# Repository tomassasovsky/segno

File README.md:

<p align="center">
  <picture>
    <source media="(prefers-color-scheme: dark)" srcset="tool/brand_assets/segno-glyph-white.svg">
    
  </picture>
</p>

<h1 align="center">Segno</h1>

<p align="center">
  A live looping instrument: a foot-operated console, two touch screens, and a
  native audio engine on a Raspberry Pi 5.
</p>

<p align="center">

</p>

Segno records a phrase, plays it back in a loop, and lets you layer more parts
over it while you keep playing. It is built as a dedicated appliance rather than
a desktop app: the musician works it with ten footswitches and an encoder,
reads it from a 15.6-inch main screen and a 7-inch readout, and never needs a
computer on stage.

This repository holds the Flutter application, the C audio engine, the console
firmware and the Yocto image that boots the appliance. The circuit boards and
the sheet-metal enclosure are in
[segno-hardware](https://github.com/tomassasovsky/segno-hardware), and the
design file in [segno-design](https://github.com/tomassasovsky/segno-design).

## What it does

- **Loops on eight tracks** in two banks of four, with record, overdub, undo
  and redo per track, mute, solo, pan, fades and reverse.
- **Five loop modes.** Multi, Sync, Song, Band and Free decide how track
  lengths relate and whether sections play together or one at a time. Tempo,
  time signature, click and count-in apply to all of them.
- **Effects** written in portable C, arranged as single effects or racks, and
  placed on live inputs, on recorded tracks, or on the outputs.
- **Virtual instruments** played from MIDI, recorded like any other input.
- **Backing tracks** that play alongside the loops.
- **A library** of saved sessions and audio, on internal storage or a USB
  drive, with search, folders, preview and backup.
- **Performance recording** to multitrack stems, with export to an Ableton
  Live set and a Mac companion app, [Segno Transfer](apps/segno_transfer/README.md),
  to download recordings over the network.
- **Control from anywhere on stage:** the built-in footswitches, external
  footswitches and expression pedals on two jacks, and MIDI over USB and DIN.
- **An appliance that maintains itself:** A/B system updates that roll back on
  failure, Wi-Fi setup, storage management and a tuner.

| Library | Loop modes |
|---|---|
|  |  |

The screenshots are renders from the application's own screenshot tests.

## Hardware

The console is a welded aluminum wedge. Its faceplate carries ten
footswitches with LED indicators (Record/Play, Stop, Undo, Mode, Track 1 to 4,
Clear and Bank), an encoder inside a 35-pixel LED ring, and the two screens.
Inside are a Raspberry Pi 5 with NVMe storage, a USB audio interface, and the
console board: a custom PCB with an RP2350 (Raspberry Pi Pico 2) that reads
the switches and drives the lights over a UART link to the Pi. The board also
provides DIN MIDI in and out, two jacks for external pedals, and USB-C Power
Delivery input.

The console firmware is a thin client. It reports raw switch, encoder and pedal
events and renders the LED frames the application sends back; all looper
behavior lives in the application.

See [segno-hardware](https://github.com/tomassasovsky/segno-hardware) for the board designs, enclosure generator
and manufacturing package, and [firmware/](firmware/README.md) for the
microcontroller code.

## Architecture

```mermaid
flowchart LR
  subgraph console["Console board (RP2350)"]
    fw["Firmware: switches, encoder, LEDs, pedal jacks"]
  end
  subgraph pi["Raspberry Pi 5, Yocto image"]
    ui["Flutter UI and blocs<br/>lib/"]
    repo["Repositories<br/>packages/*_repository"]
    engine["Audio engine in C<br/>packages/segno_engine"]
  end
  audio["USB audio interface"]
  fw <-- "UART link" --> repo
  ui --> repo --> engine
  engine <-- "miniaudio" --> audio
```

- **Application** (`lib/`). Flutter, using the bloc pattern. It runs under the
  ivi-homescreen embedder directly on DRM/KMS, one engine per screen.
- **Repositories and clients** (`packages/`). The domain layer between the UI
  and the hardware: looper state, sessions, settings, pedals, MIDI, storage,
  updates, Wi-Fi. Presentation never talks to a data client directly.
- **Audio engine** (`packages/segno_engine`). A hand-written C engine on
  [miniaudio](https://miniaud.io). The audio callback never allocates or
  blocks; the UI sends commands through a lock-free ring and reads state from
  snapshots. Dart reaches it through FFI.
- **Appliance image** (`deploy/yocto`). A Yocto build for the Raspberry Pi 5
  with RAUC A/B updates. CI builds and publishes each image.

## Repository layout

| Path | Contents |
|---|---|
| [`lib/`](lib) | The Flutter application |
| [`packages/`](packages) | Repositories, data clients and the audio engine, each with its own README |
| [`apps/segno_transfer/`](apps/segno_transfer/README.md) | Mac app for downloading performance recordings |
| [`firmware/`](firmware/README.md) | Console board and LED ring firmware |
| [`deploy/`](deploy/README.md) | Yocto layer and appliance image configuration |
| [`docs/`](docs/README.md) | Status, design records and file-format specifications |
| [`test/`](test) | Application tests, including the screenshot tests |

Two sibling repositories hold the rest of the project:
[segno-hardware](https://github.com/tomassasovsky/segno-hardware) has the PCBs
(KiCad), the enclosure generator (Python/CadQuery) and the manufacturing files,
and [segno-design](https://github.com/tomassasovsky/segno-design) has the
design's history and studies. The UI design itself is a Penpot file on a
self-hosted Penpot server; segno-design keeps snapshots of it, and the
earlier Pencil file (`segno-ui.pen`), now frozen.

## Building

Segno targets the appliance. A Mac can run the application for development,
and the mock flavor runs it without any audio hardware.

Requirements: Flutter 3.50, Xcode for the macOS host, and a C compiler for
the engine tests.

```sh
flutter pub get
flutter run -d macos --flavor development -t lib/main_mock.dart
```

Tests:

```sh
flutter test                                              # application
bash packages/segno_engine/src/test/run_native_tests.sh   # audio engine (C)
bash firmware/test/run_tests.sh                           # console link contract
```

Each package under `packages/` has its own tests; see its README. Building the
appliance image is described in [deploy/yocto](deploy/yocto/README.md), and
installing it on a Raspberry Pi in [docs/RUNNING_ON_RPI.md](docs/RUNNING_ON_RPI.md).

## Status

Segno is under active development by one person and has not had a stable
release. The application and engine run on the appliance, and experimental
images are published as
[pre-releases](https://github.com/tomassasovsky/segno/releases). The console
enclosure is designed and awaiting fabrication. Work is tracked in
[GitHub Issues](https://github.com/tomassasovsky/segno/issues), and
[docs/PROGRESS.md](docs/PROGRESS.md) records what has been built.

## Contributing

Bug reports and pull requests are welcome. Read
[CONTRIBUTING.md](CONTRIBUTING.md) first, and see [SECURITY.md](SECURITY.md)
for reporting vulnerabilities.

## License

Segno is free software, licensed under the
[GNU General Public License v3.0 or later](LICENSE). Third-party code under
`packages/segno_engine/third_party/` keeps its own licenses.

Created by [Tomás Sasovsky](https://github.com/tomassasovsky).

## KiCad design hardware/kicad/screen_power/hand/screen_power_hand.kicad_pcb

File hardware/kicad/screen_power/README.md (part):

<!-- cspell:words unreviewed -->
<!-- cspell:words IRLZ NPBF Schurter upsize -->
<!-- cspell:words fanout -->
<!-- cspell:words preorder Axicom Mbps energization Digi typec mrico kilohm -->
<!-- cspell:words overvoltage derate autosuspend overmolds fanouts onsemi Nexperia Omron derating autoroutes pulldowns -->
<!-- cspell:words SUP SUM Rds backfeed Micro pulldown Vgs Littelfuse Lumberg MMBT DMODEL stackup microstrip heatsinks eleUniverse ATOF PXCN FHAC overcurrent -->
# Screen power and touch switch

**Revision P** removes two obsolete ground-fill exclusions beside mounting
hole H1, restoring its smooth ground-copper contour. All tracks, pads,
placements and electrical connections remain unchanged. It retains each
USB cable's shield through a fifth XH contact,
so the complete cable disconnects at its plug. It retains Revision N's
through-hole power relay and removable main fuse. The four branch fuses
remain soldered to keep cost and size down.

The design retains the **two-layer, 68 × 76 mm** outline, **3 mm rounded
corners**, purple solder mask and white silkscreen. GPIO17 controls the
screen supply and both USB touch paths. Console and ring power use their
separate AUX branch. No extra Pi ribbon or USB-C module is needed.

There are **42 populated electrical references plus the F1 holder** and four
M3 mounting holes. The separate shield-drain solder pads have been removed.
The board has eight cable headers and two USB relays.
Headers have vertical pin rows, pin 1 at the bottom and retaining walls on
the left, viewed from the component side. Cables enter from above. Mounting
centers are (4, 4), (64, 4), (4, 72) and (64, 72) mm. The 3.5 mm unplated
holes have 4.25 mm copper keepouts for M3 heads/washers up to 7 mm diameter.

The USB host-presence circuit and AUX-powered data relays are retained.
Each USB shield joins board ground through XH pin 5. Host VBUS only senses connection;
it supplies neither relay coils nor screens. The selected power and fuse
changes are described in the
[implementation plan](../../../docs/plan/2026-09-27-screen-power-stock-cost-1072-plan.md)
and [fuse/coil assessment](../../../docs/reviews/screen-power-stock-cost-1072/holder-coil-budget.md).

The [manufacturing record](../../../docs/reviews/pcb-finish-all-three-1072/manufacturing-zips.json)
identifies the verified manufacturing archives and their board hashes. Use
those archives rather than exporting an unreviewed working copy. Revision I
remains withdrawn because of incorrect
USB relay common connections. The corrected commons 3/6 and normally open
contacts 4/5 remain unchanged. No pre-PCB prototype or further owner
measurements are required. Design review cannot establish assembled USB
compliance, exact shutdown timing or enclosure temperature.
Issue: [#1072](https://github.com/tomassasovsky/segno/issues/1072).

## Wiring

| Connector | Function |
| --- | --- |
| J1, JST VH 2-pin | Dedicated AUX input: pin 1 = +5 V, pin 2 = ground. Use the existing nominal 5 V buck. The assessed coil-drive envelope requires **4.75–5.25 V at J1**, before onboard F1 and its holder; this is not a guarantee of either screen's minimum operating voltage. |
| J2, JST XH 2-pin | Console J25 control. Pin 1 = BCM GPIO17; pin 2 = ground. One two-wire cable, numbered pins connected 1:1. |
| J101 / J201, JST XH 5-pin | USB-A male donor tails from each Pi USB 2.0 host port; channels 1 / 2. |
| J102 / J202, JST XH 5-pin | USB-C male donor tail to UPERFECT (channel 1), and Micro-B male donor tail to APROTII (channel 2). |
| J103 / J203, JST VH 2-pin | Screen power outputs. Pin 1 = switched +5 V; pin 2 = ground. Feed the separate screen power leads; final cable termination remains to be selected. |

The existing Pi-to-console ribbon stays directly connected. Console J25 takes
GPIO17 from physical Pi pin 11. This board has no 40-pin header and takes no
screen power from Pi GPIO. GPIO high enables both channels; low, disconnected,
or an unpowered Pi defaults them off. The Pi, board, HDMI and screens share ground.
Each USB plug carries VBUS, D−, D+, ground and shield together; see the cable
contract below.

### What “off” means

With AUX still powered, a low or disconnected GPIO17 turns off the shared
screen supply and opens both USB data paths. The main power connectors and
USB-touch VBUS all come from that switched supply; Pi host VBUS does not
feed the screens. An electrically unpowered Pi therefore defaults the board
off even if the dedicated screen buck remains powered.

A software-halted Pi that still has input power must explicitly release or
lower GPIO17. R2 is 4.7 kΩ, 1%, to shunt weak pull-ups on a released signal.
The assessed weak-source case is at most 3.63 V through at least 50 kΩ:
Including resistor tolerances and a 1 µA injected-leakage allowance, Q1's
unloaded base stays below 0.314 V, within the 0.35 V base-bias design budget.
This is a design envelope, not a guaranteed RP1 pull-resistor specification;
leave the internal pull disabled. An actively driven high still enables the
board. The board follows this signal; it does not detect Linux shutdown
or missing HDMI. The appliance now includes a dedicated GPIO owner and Weston
start/stop hooks: enable before display probing, then drive low before stopping
HDMI. Its five-second discharge wait is provisional until measured on both
screens. These changes are locally tested, not deployed to the inspected Pi.
On 2026-09-22 the
owner confirmed that both actual displays go fully dark with their power and
touch USB disconnected and HDMI left connected, following the Pi-on test.
This closes the HDMI-only visual check for this setup; GPIO-controlled cutoff
and shutdown timing still need assembled-device validation.

### XH USB cable contract

The committed PCB footprint is
`Connector_JST:JST_XH_B5B-XH-A_1x05_P2.50mm_Vertical`, with
**B5B-XH-A(LF)(SN)** board headers and **XHP-5** mating housings. It is a
2.50 mm pitch, shrouded friction-retained connector with 1.10 mm nominal finished PCB holes.
Use the exact five-position parts in the
[JST XH drawing](https://www.jst-mfg.com/product/pdf/eng/eXH.pdf).
The active harness is assembled from suitable existing USB donor cables;
the earlier ready-made four-pin cable selection is superseded.

All four headers use the following pin map. Read the numbered PCB pads and
bottom-side labels, not wire colors or a mirrored view of the cable housing.

| PCB pin | Signal | Input J101/J201 | Output J102/J202 |
| --- | --- | --- | --- |
| 1 | +5 V | Pi VBUS; low-current host detection only | Fused switched touch supply |
| 2 | D− | Host data | Screen data |
| 3 | D+ | Host data | Screen data |
| 4 | GND | Common ground | Common ground |
| 5 | Shield | Cable shield to board GND | Cable shield to board GND |

One USB-A-to-USB-C donor and one USB-A-to-Micro-B donor can supply the four
touch tails, retaining their factory USB plugs and overmolds. Use shielded
USB 2.0 high-speed data cables with an intact controlled pair, not charge-only
leads. Establish conductor size and insulation diameter from the exact cable
specification or the exposed donor; neither is known for the owner's existing
cables. The owner confirmed that the available cables physically reach their
installed destinations. This closes the earlier reach concern; it does not
establish wire gauge, insulation diameter, shielding or USB performance.
Measure and cut the completed tails to the retained assessed
length limits: **30 cm per host tail, 25 cm for the USB-C touch tail and
30 cm for the Micro-B touch tail**, including service slack. If a measured
route exceeds a limit, resolve placement or assess the longer complete USB
channel before accepting the harness; the connector change does not establish
enclosure fit.

Use four XHP-5 housings and **20 new contacts**, five per cable. The specified
**SXH-001T-P0.6** contact accepts 28–22 AWG conductors and **0.9–1.9 mm
insulation outside diameter**. Both limits must hold, including at pin 5.
Use matching crimp tooling and inspect contact retention and insulation support.
Do not force an unsuitable donor wire into this contact or fold strands to
make it fit. A different conductor/insulation range needs a documented compatible
termination before assembly.

The two separate main-power leads remain: one USB-C lead to UPERFECT and one
Micro-B lead to APROTII, connected to J103/J203 through the larger two-pin VH
harness. The XH touch cables carry a **500 mA design allocation**, not the
screen's main power.
The host lead's VBUS feeds approximately 50 µA of presence-sensing load at
the upper 5.5 V host corner. AUX supplies the relay coils. Screen touch current must
be measured with both screen connectors attached; a screen may join the
supplies internally, and the 800 mA fuse is not an active 500 mA limiter.

Before connecting equipment, measure each cable's pin-to-contact continuity,
including USB shell to pin 5, and check for shorts. Retain the USB-C donor's
proper legacy-source configuration (56 kilohm Rp to VBUS) inside its plug;
test both plug orientations. XH pin 5 is shield, not CC. An unknown plug's
current advertisement must not be inferred from wire colors or connector shape.
USB speed, voltage drop and cable temperature remain first-assembly acceptance
checks. Factory cable certification does not certify a cut cable and PCB channel.

Keep each cable's foil/braid and twisted data pair intact up to the shortest
practical fanout. Terminate the shield at **pin 5 in the same removable plug**.
Use a short insulated drain termination within the contact's conductor and
insulation ranges; if the bare drain cannot be crimped correctly, join it to
a short suitable insulated wire and insulate the joint. Keep this shield
breakout at most **10 mm** as a construction target and secure the cable jacket
so pulling the cable does not load the individual contacts. The five-pin plug's
local fanout fit must be checked with the actual donor; the old side-solder-pad
fit assessment does not establish it. Keep pin 4 as the dedicated power return;
do not use foil or loose braid for load current. No shield wire is separately
soldered to the PCB: unplugging the XH housing disconnects all five conductors.
See the [current harness notes](../../../docs/reviews/screen-power-ground-cleanup-1072/harness.md)
for quantities, procurement and inspection details.

**Both USB-C leads to the 15.6in screen need a real ground wire.** On the first
assembled console (2026-10-17) a donor cable with no insulated ground conductor,
which returns ground only through its shield, made the 15.6in screen unstable.
Before cutting a donor for J102 or the J103 power lead, confirm it has a
separate ground conductor (black in a standard USB cable) and meter the plug's
GND pin to that wire. A shield-only cable can still serve a Pi host tail
(J101/J201), whose VBUS carries only the host-presence current; crimp its drain
into both pin 4 and pin 5 there.

### Separate main-power harness

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
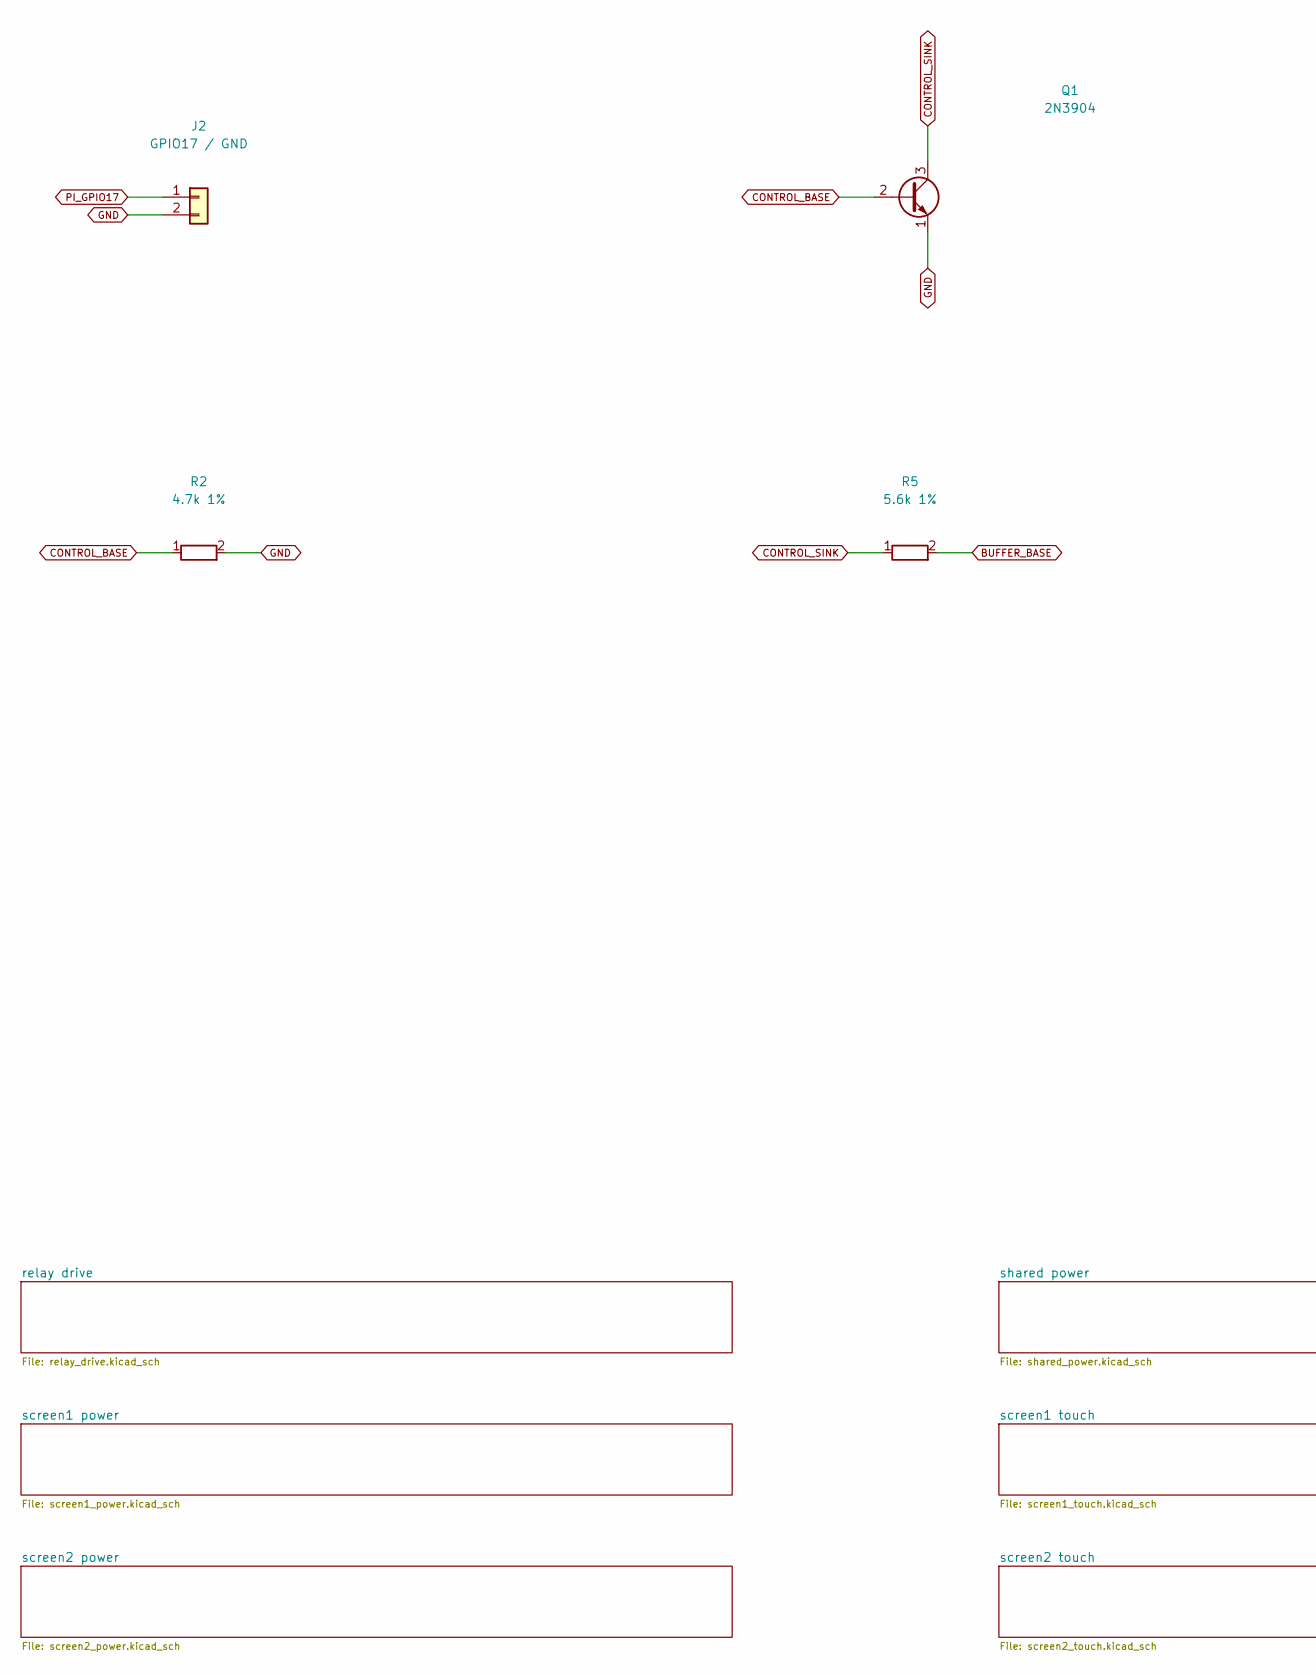
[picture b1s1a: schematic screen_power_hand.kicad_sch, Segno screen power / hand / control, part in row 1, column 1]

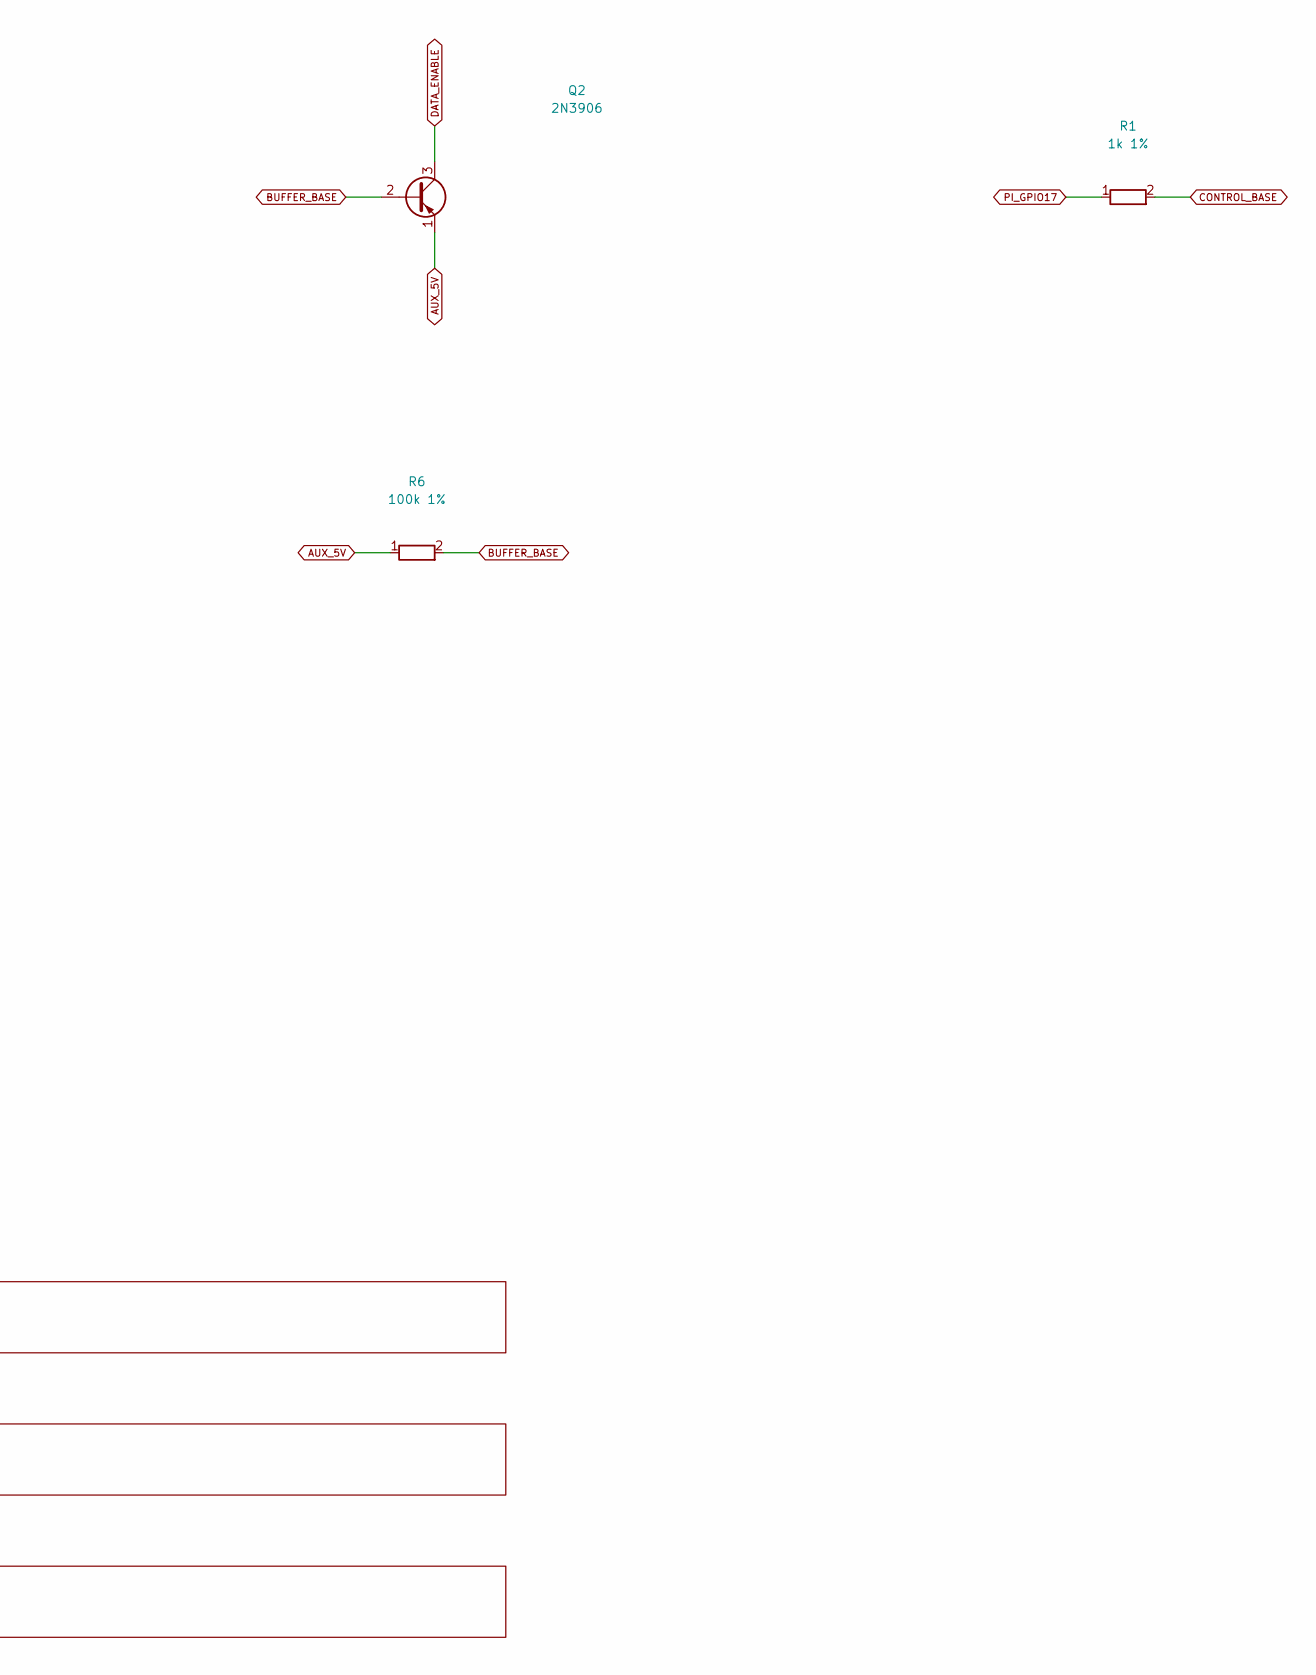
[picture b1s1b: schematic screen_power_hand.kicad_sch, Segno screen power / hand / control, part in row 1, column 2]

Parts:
J2: GPIO17 / GND; JST_XH_B2B-XH-A_1x02_P2.50mm_Vertical; MPN B2B-XH-A(LF)(SN)
Q1: 2N3904; TO-92_Inline_Wide; MPN 2N3904BU
Q2: 2N3906; TO-92_Inline_Wide; MPN 2N3906BU
R1: 1k 1%; R_Axial_DIN0207_L6.3mm_D2.5mm_P10.16mm_Horizontal; MPN MFR-25FBF52-1K
R2: 4.7k 1%; R_Axial_DIN0207_L6.3mm_D2.5mm_P10.16mm_Horizontal; MPN MFR-25FBF52-4K7
R5: 5.6k 1%; R_Axial_DIN0207_L6.3mm_D2.5mm_P10.16mm_Horizontal; MPN MFR-25FBF52-5K6
R6: 100k 1%; R_Axial_DIN0207_L6.3mm_D2.5mm_P10.16mm_Horizontal; MPN MFR-25FBF52-100K

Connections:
AUX_5V: Q2.1 (E), R6.1; also elsewhere on the board
BUFFER_BASE: Q2.2 (B), R5.2, R6.2
CONTROL_BASE: Q1.2 (B), R1.2, R2.1
CONTROL_SINK: Q1.3 (C), R5.1
DATA_ENABLE: Q2.3 (C); also elsewhere on the board
GND: J2.2, Q1.1 (E), R2.2; also elsewhere on the board
PI_GPIO17: J2.1, R1.1

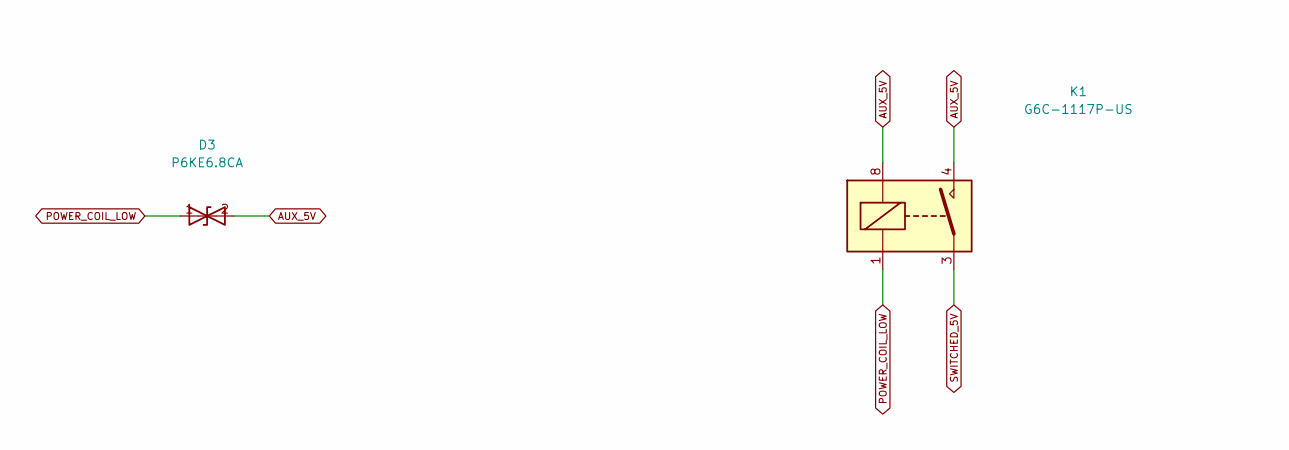
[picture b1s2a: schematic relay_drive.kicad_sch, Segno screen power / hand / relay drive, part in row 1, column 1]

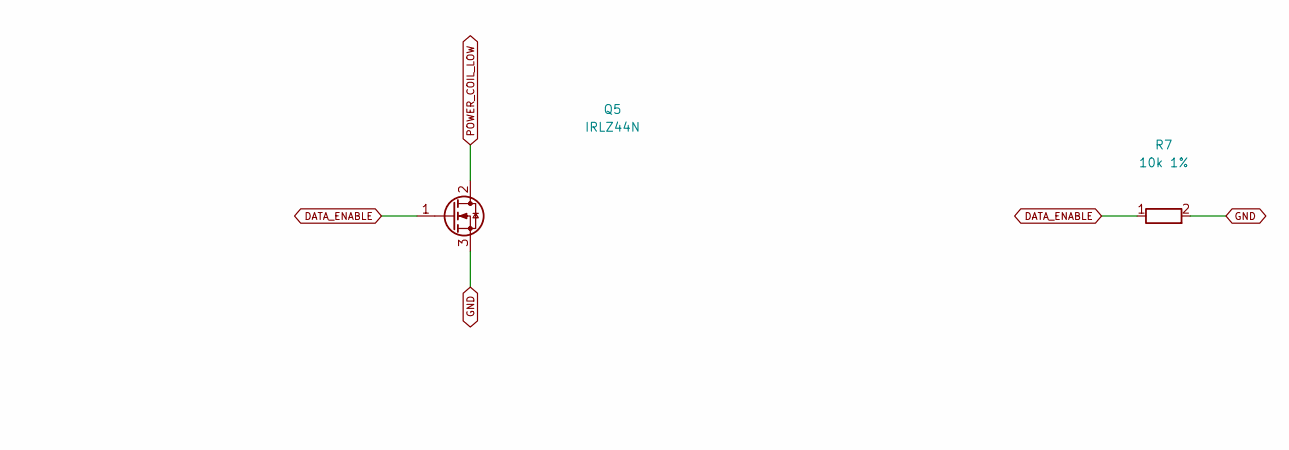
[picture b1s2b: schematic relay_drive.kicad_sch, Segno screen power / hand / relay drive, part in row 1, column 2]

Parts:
D3: P6KE6.8CA; D_DO-15_P10.16mm_Horizontal; MPN P6KE6.8CA
K1: G6C-1117P-US; Relay_Omron_G6C-1117P-US; MPN G6C-1117P-US DC5
Q5: IRLZ44N; TO-220-3_IRLZ44N; MPN IRLZ44NPBF
R7: 10k 1%; R_Axial_DIN0207_L6.3mm_D2.5mm_P10.16mm_Horizontal; MPN MFR-25FBF52-10K

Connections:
AUX_5V: D3.2 (A2), K1.4 (NO), K1.8 (COIL+); also elsewhere on the board
DATA_ENABLE: Q5.1 (G), R7.1; also elsewhere on the board
GND: Q5.3 (S), R7.2; also elsewhere on the board
POWER_COIL_LOW: D3.1 (A1), K1.1 (COIL-), Q5.2 (D)
SWITCHED_5V: K1.3 (NO); also elsewhere on the board

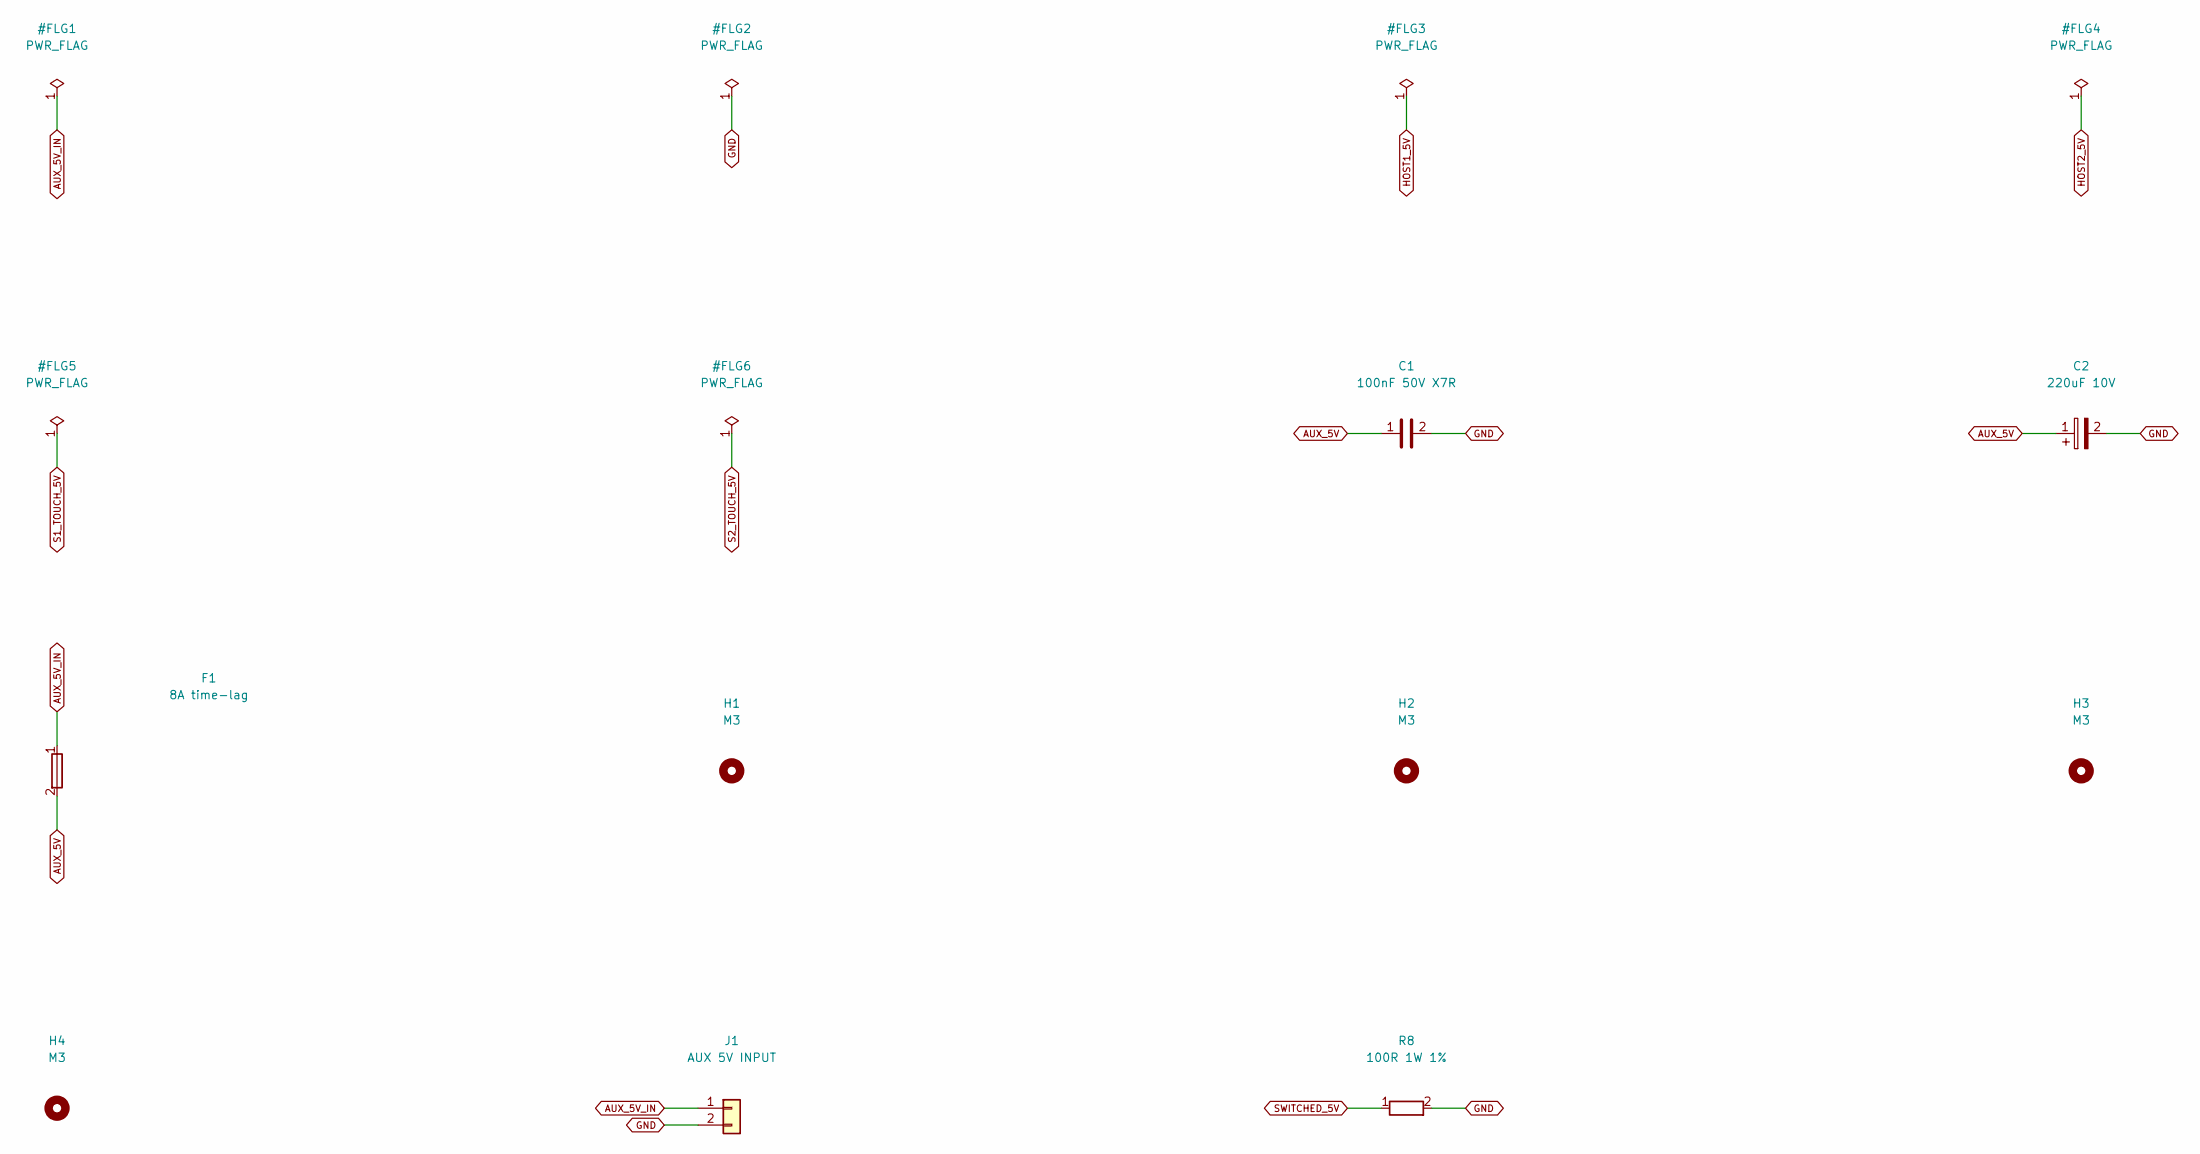
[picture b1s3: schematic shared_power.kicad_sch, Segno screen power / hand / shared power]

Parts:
C1: 100nF 50V X7R; C_Disc_D7.5mm_W4.4mm_P5.00mm; MPN K104K10X7RF53H5
C2: 220uF 10V; CP_Radial_D6.3mm_P2.50mm; MPN EEU-FR1A221
F1: 8A time-lag; Fuseholder_Schurter_OGN_0031.8201; MPN 0001.2513
H1, H2, H3, H4: M3; MountingHole_3.5mm; MPN NPTH
J1: AUX 5V INPUT; JST_VH_B2P-VH_1x02_P3.96mm_Vertical; MPN B2P-VH(LF)(SN)
R8: 100R 1W 1%; R_Axial_DIN0207_L6.3mm_D2.5mm_P10.16mm_Horizontal; MPN PR01000101000FA100

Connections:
AUX_5V: C1.1, C2.1, F1.2; also elsewhere on the board
AUX_5V_IN: F1.1, J1.1
GND: C1.2, C2.2, J1.2, R8.2; also elsewhere on the board
SWITCHED_5V: R8.1; also elsewhere on the board

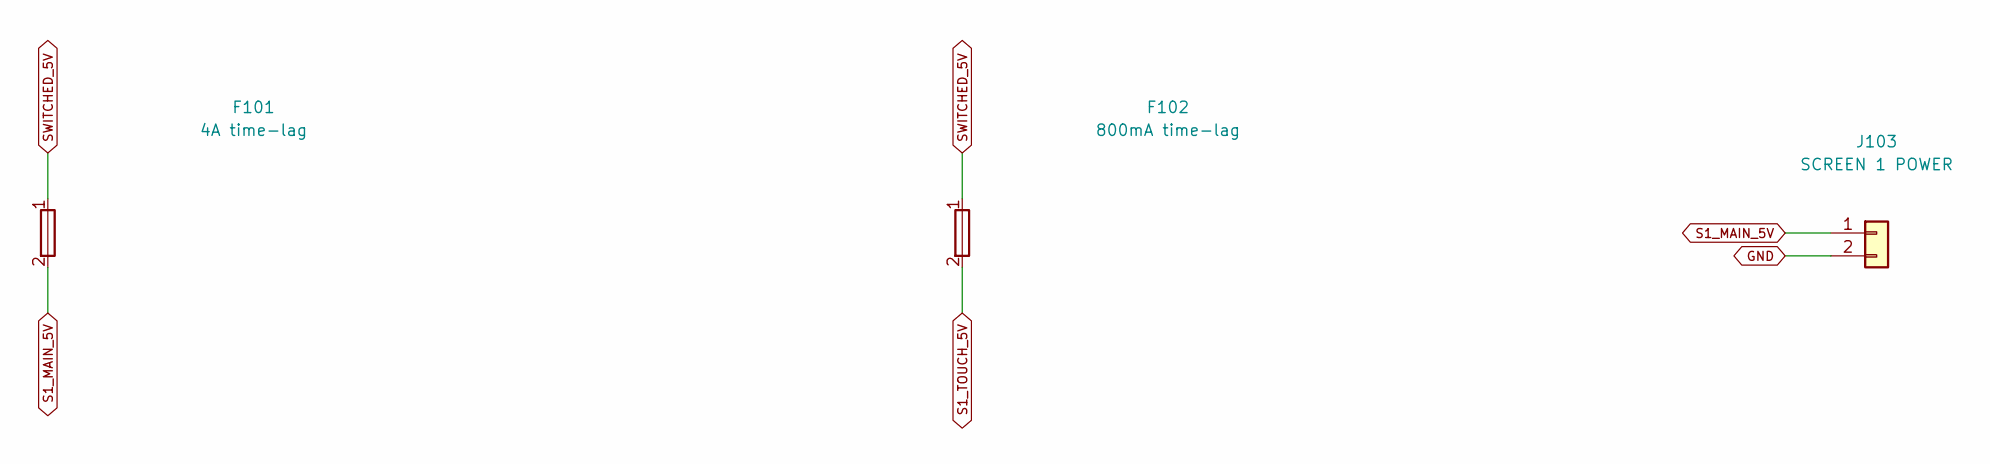
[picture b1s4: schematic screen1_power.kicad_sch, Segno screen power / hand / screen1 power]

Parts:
F101: 4A time-lag; Fuse_Bel_0697H_P5.08mm; MPN 0697H4000-02
F102: 800mA time-lag; Fuse_Bel_0697H_P5.08mm; MPN 0697H0800-02
J103: SCREEN 1 POWER; JST_VH_B2P-VH_1x02_P3.96mm_Vertical; MPN B2P-VH(LF)(SN)

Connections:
GND: J103.2; also elsewhere on the board
S1_MAIN_5V: F101.2, J103.1
S1_TOUCH_5V: F102.2; also elsewhere on the board
SWITCHED_5V: F101.1, F102.1; also elsewhere on the board

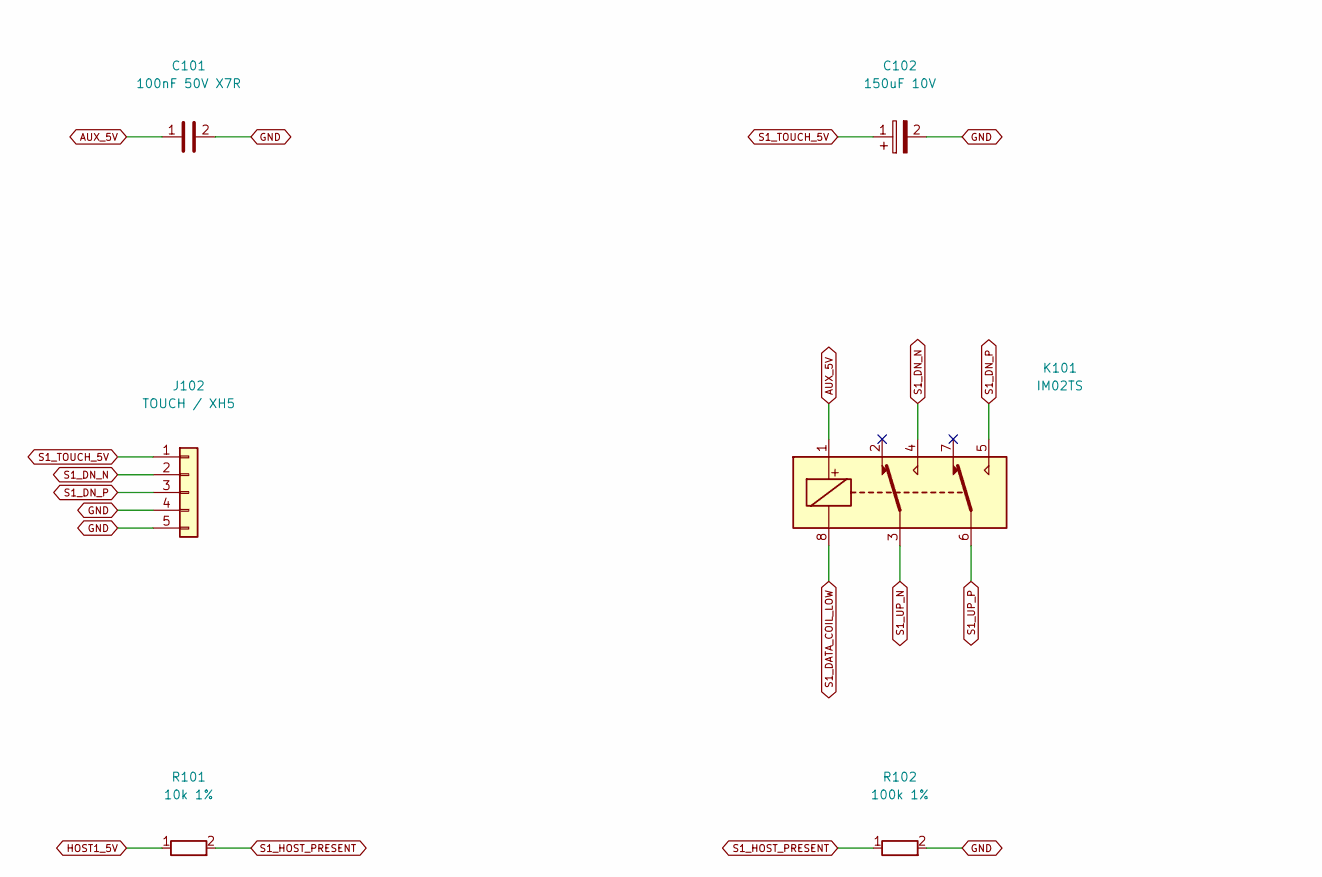
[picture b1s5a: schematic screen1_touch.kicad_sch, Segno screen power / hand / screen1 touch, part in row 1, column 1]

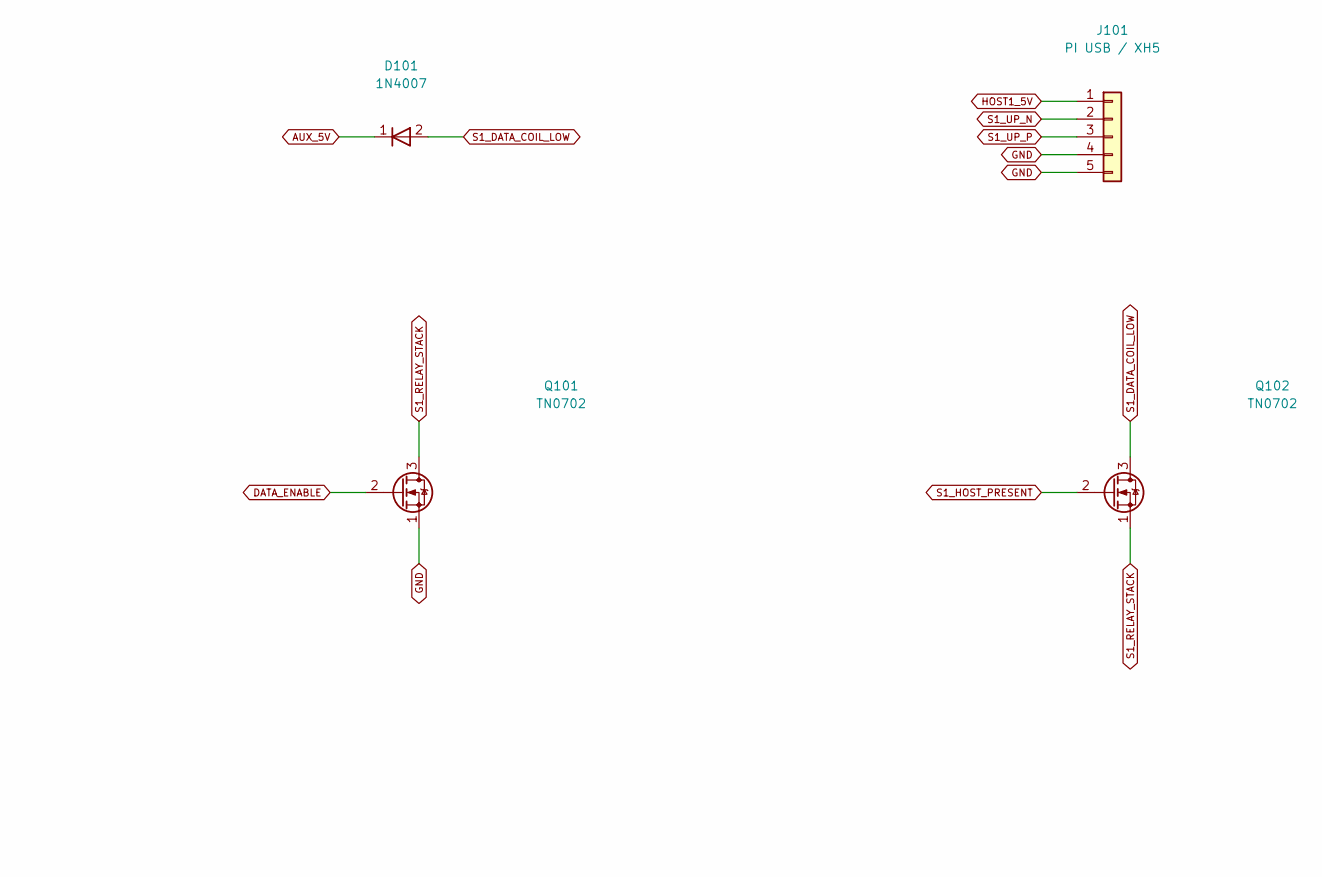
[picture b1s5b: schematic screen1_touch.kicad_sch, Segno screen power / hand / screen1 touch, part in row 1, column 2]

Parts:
C101: 100nF 50V X7R; C_Disc_D7.5mm_W4.4mm_P5.00mm; MPN K104K10X7RF53H5
C102: 150uF 10V; CP_Radial_D5.0mm_P2.00mm; MPN EEU-FR1A151
D101: 1N4007; D_DO-41_SOD81_P10.16mm_Horizontal; MPN 1N4007G
J101: PI USB / XH5; JST_XH_B5B-XH-A_1x05_P2.50mm_Vertical; MPN B5B-XH-A(LF)(SN)
J102: TOUCH / XH5; JST_XH_B5B-XH-A_1x05_P2.50mm_Vertical; MPN B5B-XH-A(LF)(SN)
K101: IM02TS; Relay_DPDT_AXICOM_IMSeries_Pitch5.08mm_D0.90mm; MPN 1-1462037-3
Q101, Q102: TN0702; TO-92_Inline_Wide; MPN TN0702N3-G
R101: 10k 1%; R_Axial_DIN0207_L6.3mm_D2.5mm_P10.16mm_Horizontal; MPN MFR-25FBF52-10K
R102: 100k 1%; R_Axial_DIN0207_L6.3mm_D2.5mm_P10.16mm_Horizontal; MPN MFR-25FBF52-100K

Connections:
AUX_5V: C101.1, D101.1 (K), K101.1; also elsewhere on the board
DATA_ENABLE: Q101.2 (G); also elsewhere on the board
GND: C101.2, C102.2, J101.4, J101.5, J102.4, J102.5, Q101.1 (S), R102.2; also elsewhere on the board
HOST1_5V: J101.1, R101.1
S1_DATA_COIL_LOW: D101.2 (A), K101.8, Q102.3 (D)
S1_DN_N: J102.2, K101.4
S1_DN_P: J102.3, K101.5
S1_HOST_PRESENT: Q102.2 (G), R101.2, R102.1
S1_RELAY_STACK: Q101.3 (D), Q102.1 (S)
S1_TOUCH_5V: C102.1, J102.1; also elsewhere on the board
S1_UP_N: J101.2, K101.3
S1_UP_P: J101.3, K101.6

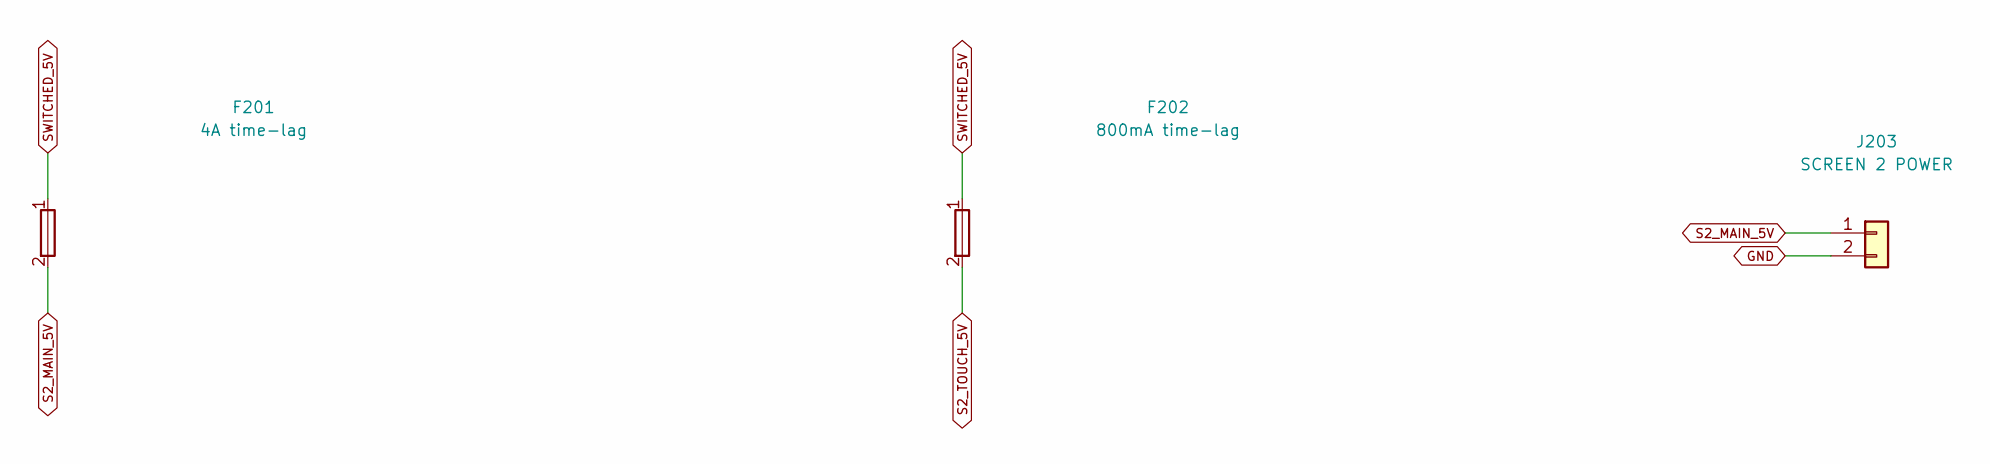
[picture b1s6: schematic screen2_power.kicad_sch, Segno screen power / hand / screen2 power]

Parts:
F201: 4A time-lag; Fuse_Bel_0697H_P5.08mm; MPN 0697H4000-02
F202: 800mA time-lag; Fuse_Bel_0697H_P5.08mm; MPN 0697H0800-02
J203: SCREEN 2 POWER; JST_VH_B2P-VH_1x02_P3.96mm_Vertical; MPN B2P-VH(LF)(SN)

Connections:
GND: J203.2; also elsewhere on the board
S2_MAIN_5V: F201.2, J203.1
S2_TOUCH_5V: F202.2; also elsewhere on the board
SWITCHED_5V: F201.1, F202.1; also elsewhere on the board

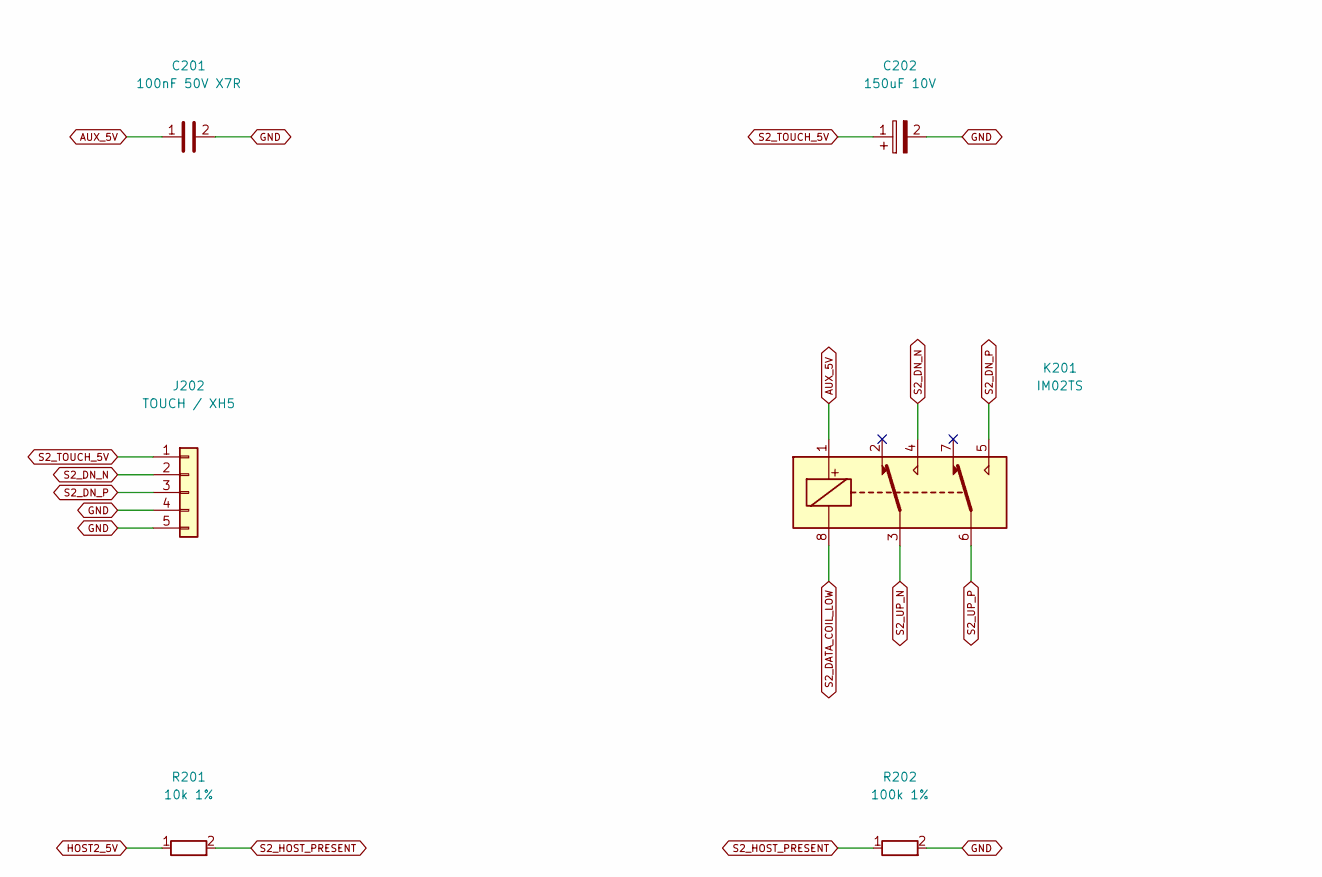
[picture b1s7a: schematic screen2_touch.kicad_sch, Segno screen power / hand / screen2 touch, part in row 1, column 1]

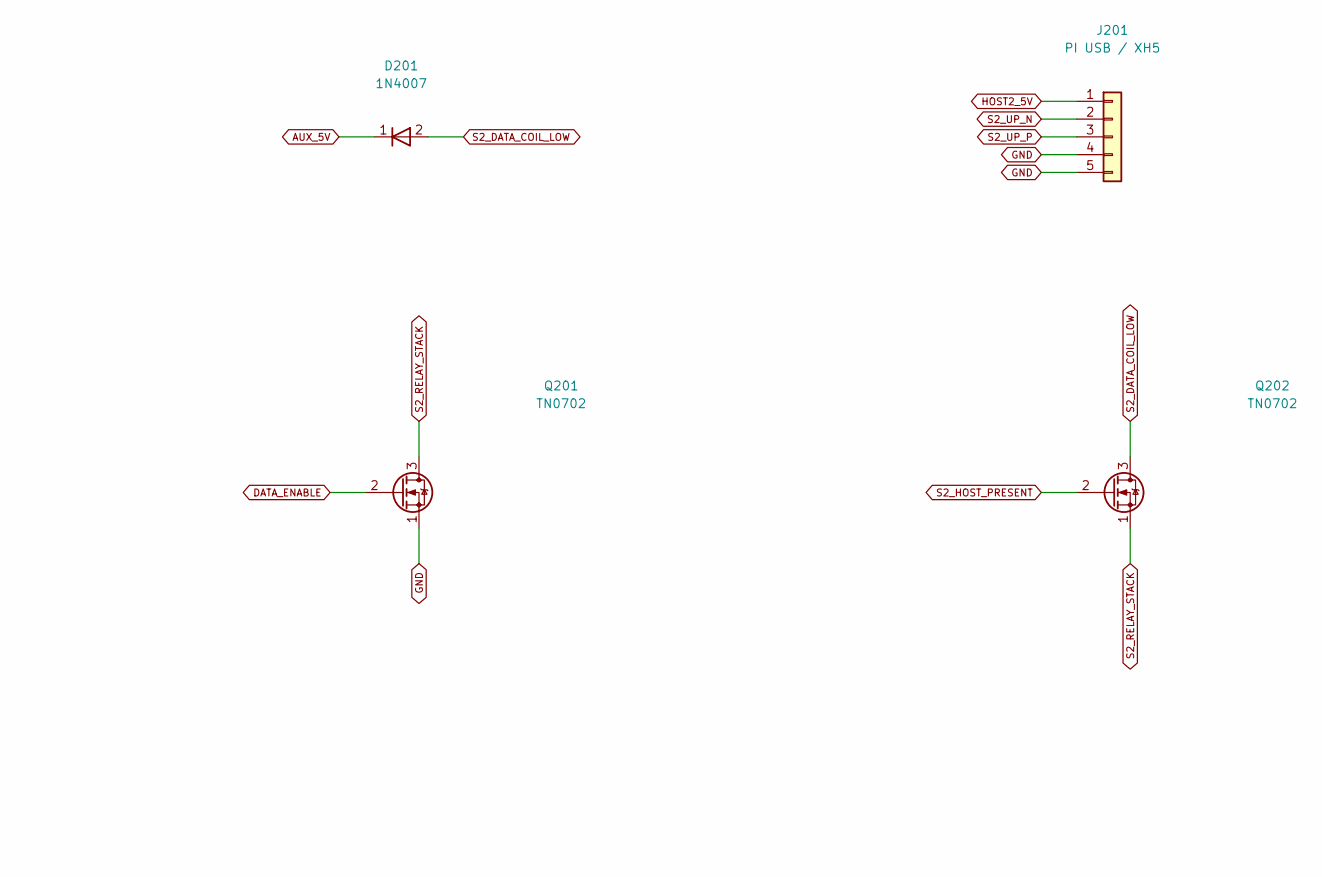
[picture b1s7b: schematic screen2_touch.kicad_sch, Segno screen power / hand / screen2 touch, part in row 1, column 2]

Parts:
C201: 100nF 50V X7R; C_Disc_D7.5mm_W4.4mm_P5.00mm; MPN K104K10X7RF53H5
C202: 150uF 10V; CP_Radial_D5.0mm_P2.00mm; MPN EEU-FR1A151
D201: 1N4007; D_DO-41_SOD81_P10.16mm_Horizontal; MPN 1N4007G
J201: PI USB / XH5; JST_XH_B5B-XH-A_1x05_P2.50mm_Vertical; MPN B5B-XH-A(LF)(SN)
J202: TOUCH / XH5; JST_XH_B5B-XH-A_1x05_P2.50mm_Vertical; MPN B5B-XH-A(LF)(SN)
K201: IM02TS; Relay_DPDT_AXICOM_IMSeries_Pitch5.08mm_D0.90mm; MPN 1-1462037-3
Q201, Q202: TN0702; TO-92_Inline_Wide; MPN TN0702N3-G
R201: 10k 1%; R_Axial_DIN0207_L6.3mm_D2.5mm_P10.16mm_Horizontal; MPN MFR-25FBF52-10K
R202: 100k 1%; R_Axial_DIN0207_L6.3mm_D2.5mm_P10.16mm_Horizontal; MPN MFR-25FBF52-100K

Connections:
AUX_5V: C201.1, D201.1 (K), K201.1; also elsewhere on the board
DATA_ENABLE: Q201.2 (G); also elsewhere on the board
GND: C201.2, C202.2, J201.4, J201.5, J202.4, J202.5, Q201.1 (S), R202.2; also elsewhere on the board
HOST2_5V: J201.1, R201.1
S2_DATA_COIL_LOW: D201.2 (A), K201.8, Q202.3 (D)
S2_DN_N: J202.2, K201.4
S2_DN_P: J202.3, K201.5
S2_HOST_PRESENT: Q202.2 (G), R201.2, R202.1
S2_RELAY_STACK: Q201.3 (D), Q202.1 (S)
S2_TOUCH_5V: C202.1, J202.1; also elsewhere on the board
S2_UP_N: J201.2, K201.3
S2_UP_P: J201.3, K201.6

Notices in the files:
README.md:
License: GPL-3.0-or-later
parts and their libraries:
XIAO_Module.step is therefore vendored from github.com/Tircown/ERCF-easy-brd (Kicad/ercf-easy-brd.pretty/packages3d/Seeeduino Xiao.step), which is GPL-3.0 and so compatible with this repo.
